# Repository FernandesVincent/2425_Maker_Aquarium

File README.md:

<header style="
      background-color: #004080;
      color: white;
      padding: 1rem;
      text-align: center;
      height: auto;">
<div class="header-title">
<h1>Aquarium Automatisé</h1>
</div>
</header>

SOMMAIRE
- Préambule
- Objectifs du projet
- Meuble
- Filtration
- Test en gouttes
- Raspberry Pi
- PCB
- Écrans
- Code
- Câblage
- Résultat et Conclusion
- Futur du projet
<h1 style="text-align: center; text-decoration: underline; font-weight: bold;">Préambule</h1>
Aujourd'hui, lorsqu'un particulier achète son aquarium il doit pouvoir gérer un nombre important de facteurs comme la température du bac, la distribution de la nourriture mais également les différents test que peux nécessité son Aquarium (ph, NO2, CO2, etc...). C'est donc dans l'idée de soulager les personnes que cela pèse de devoir s'occuper de tout ça que l'idée du projet d'aquarium automatisé et connecté m'est venue à l'esprit.
<h1 style="text-align: center; text-decoration: underline; font-weight: bold;">Objectifs du Projet</h1>
Pour répondre à la problématique énoncée durant le préambule, j'ai dessiné les différents axes et objectifs du projet énoncés ci-dessous:
- Automatisation des changements d'eau
- Contrôle simple et total sur la luminosité
- Automatisation de la distribution de la nourriture
- Automatisation des test en gouttes
- Contrôle simple de la température
- Afficher le tout sur des écrans
- Bonus : Créer une Application mobile
Afin de réaliser l'ensemble de ces objectifs, j'ai du mettre en oeuvre plusieurs compétences que j'ai pu apprendre durant mon cursus à l'ENSEA telles que:
- Découpe LASER
- Conception de PCBs
- Modélisation et impression 3D
- Sertissage de câbles
- Mécanique
- Soudure
Mais également de nouvelles comme le montage vidéo et le HTML/CSS/JS pour la création d'un site. Pour expliquer chaque partie de ce projet en détail, nous allons partir du plus gros oeuvre vers le plus petit. Commençons donc par parler du meuble qui doit supporter l'aquarium.
<h1 style="text-align: center; text-decoration: underline; font-weight: bold;">Meuble</h1>
Au vu de l'ensemble des objectifs du projet, il fallait un endroit où ranger notamment, l'électronique avec les PCBs et les câbles, le bloc de filtration externe, le dispositif d'analyse des test en gouttes ainsi que les bacs de changements d'eau. Pour répondre à ce besoin j'ai penser à la création d'un meuble pouvant supporter le poids de l'aquarium ainsi que tout ce qu'il y a à l'intérieur. Pour ce faire il a été décidé que la structure du meuble se ferait à l'aide de profilé aluminium 20x40mm et que les murs seront faits en MDF 3mm. Cependant quelques contraintes étaient présentes:
- le meuble doit au minimum faire la largeur (30cm) et la longueur(60cm) de l'aquarium.
- Il doit pouvoir accueillir 2 bacs ayant au minimum une capacité de 18L.
- Le bac doit être assez petit pour diminuer les coûts liés au profilé aluminium.
Prenant tout cela en compte, j'ai réalisés des premiers modèles 3D pour pouvoir estimer la taille du meuble et la quantité de profilé aluminium ainsi que de MDF nécessaire. Vous pouvez voir les modèles prototypes ci-dessous:
<table>
<tbody>
<tr>
<td></td>
<td></td>
<td></td>
</tr>
</tbody>
</table>
<table>
<tbody>
<tr>
<td></td>
<td></td>
<td></td>
</tr>
</tbody>
</table>
La version finale étant la suivante :

L'ensemble des fichiers STL est disponible sur mon
<a href="https://github.com/FernandesVincent/2425_Maker_Aquarium">GitHub</a>
dans la catégorie "onshape".
Ce meuble est donc sur 2 étages, le premier étant un étage réservé aux trois bacs de changements d'eau. Chacun ayant un objectif unique:
<br/>
<br/>
Celui ci-dessous est dédié à l'eau usée de l'aquarium qui peut être réutilisée pour par exemple arroser ses plantes.

Le second présent ci-dessous est fait pour accueillir l'eau propre qui va venir remplacer l'eau usée.

Le troisième et plus petit doit est quant à lui réservé à l'eau en sortie des test à gouttes qui doit être jetée.

Pour la sortie du premier bac j'ai trouver un modèle 3D de robinet qui fonctionne assez bien sur
<a href="https://www.printables.com/model/278618-water-tap">Printables</a>
.
De même que précédemment l'ensemble des fichiers STL mais également les fichiers DXF sont disponibles sur mon
<a href="https://github.com/FernandesVincent/2425_Maker_Aquarium">GitHub</a>
dans la catégorie "onshape".
<h1 style="text-align: center; text-decoration: underline; font-weight: bold;">Filtration</h1>
<br/>
Attaquons le second étage du meuble par la partie concernant le bloc de filtration. J'ai souhaité faire ce bloc externe moi-même car cela me permettait de créer un design personnalisé, notamment pour pouvoir y placer aisément le chauffage et la sonde ph en plus des masses filtrantes.
<br/>
Comme précédemment vous pouvez voir ci-dessous le prototype de ce bloc de filtration suivi de la version finale,
<br/>
<br/>
prototype:

<br/>
version finale:

<br/>
<br/>
Pour pouvoir nettoyer les masses filtrantes, j'ai designer un bac de remonté (trouer pour que l'eau s'en écoule et ne pas trempé le meuble en les sortant) avec sa poignée :
<table>
<tbody>
<tr>
<td></td>
<td></td>
</tr>
</tbody>
</table>
<br/>
<br/>
Concernant les différents composants de ce bloc, la sonde ph vient de
<a href="https://wiki.dfrobot.com/Gravity__Analog_Spear_Tip_pH_Sensor___Meter_Kit__For_Soil_And_Food_Applications__SKU__SEN0249">DFRobot</a>
tandis que le chauffage est fournis avec l'aquarium qui est un aquarium de 60L de la marque CIANO disponible sur
<a href="https://www.amazon.fr/Aquarium-Poissons-Consommables-Chauffage-Emballage/dp/B0DMZ6JCDD/?_encoding=UTF8&amp;pd_rd_w=eTX08&amp;content-id=amzn1.sym.46807d81-91bd-498b-9732-d523d8e7a752%3Aamzn1.symc.fc11ad14-99c1-406b-aa77-051d0ba1aade&amp;pf_rd_p=46807d81-91bd-498b-9732-d523d8e7a752&amp;pf_rd_r=917652W8GSPYV4HS716T&amp;pd_rd_wg=m7z8E&amp;pd_rd_r=916570f0-c766-4f99-b61e-7f823d6b24d8&amp;ref_=pd_hp_d_atf_ci_mcx_mr_ca_hp_atf_d&amp;th=1">Amazon</a>
.
<br/>
De plus, concernant les masses filtrantes elles sont également disponibles sur Amazon:
<a href="https://www.amazon.fr/Fluval-Pr%C3%A9filtre-pour-Aquariophilie-750/dp/B001CZXZEU?crid=2DO1R98ZQM2RC&amp;dib=eyJ2IjoiMSJ9.NOtwUJAeSHLB4A1TeyF7lMZri_mYYibux8elORv2TfHT8yLHpVdMSdJHqTUiYHcFMGr334v6IEnsWWmJfPLGE1mpoogN8XoEghupyyNrigO5VS3plDP2CcTmYq2QG4MJTkvTzTTOcQFQ4Y0zzN6mUG_yH7nay19Ffslt9v3t-JCdI6s2QMdTKHUrgb4h_1CvccY8n2z9cqhy9a3K2YmWuXX8cIhYSCcO7GUgdoUt6KjcFyZBTqqU88QPV-2foIqJT7tRuESUFezL2JtSR4yoJJafDqbmSgWf8wqJXLkooE1-nc9v4LDAB3mVxILasvuHKCNPN2AHisuPH9ZROWr5dpat5z9vd5tvAiF1vmKVE2g3hL_7fAWg2CkyKnFiSWWdrk5zkhM4B4p-2tI30VVCbNROYQcaY3yV6V1a9vud8sK52BZ7lmUmHwG4r6HhVILX.sY-sm_8FTIMCC4HghsrVIvfEG4izV4uUMwokH-4gn60&amp;dib_tag=se&amp;keywords=ceramique%2Bfiltre%2Baquarium&amp;qid=1740995166&amp;sprefix=ceramique%2Bfiltre%2Baquarium%2Caps%2C81&amp;sr=8-1&amp;th=1">céramique</a>
;
<a href="https://www.amazon.fr/cyclingcolors-d%C3%A9couper-300x210mm-Universelle-%C3%A9paisseur/dp/B0B8JQTZXK?__mk_fr_FR=%C3%85M%C3%85%C5%BD%C3%95%C3%91&amp;crid=1GWVJFUSDAMSF&amp;dib=eyJ2IjoiMSJ9.-Nc9EyO1uODmLOWsuEoIv2-ijdhS7vjX1hI6M1EGydp_XFS0wtrzbE2jVMFgrEHocHL6DNbcq4DOPNmEpaNBjZdWuUZP7ZPMicQLsIZ90SWD_deMd8pHQZAqzOpOAZ4D1IFHZ2X0fnkMDess7XfQdBE53jzyoQ5U7YxbRgxUxo4TxXIPRLPpCA1pShM8uPEC_14BnQmFSo0ENJEtF6zNZXzpbQdPOGYKqjRVUeZF0_ePPmf3qAuxzeko5WCX9S8S1h26QB7Ui_yH5xzVT67D3-7iV_G0tFTnQTAvHnabRmVddSMM1xzyo7R-AJKU_j0SQG36PPXQcBq1ewFXpCj_3ksSo4r8ET7GnpSYFM6XmYWrbgCw1QJ-D-15VbdYH-UsJ4eVRgI1szYcRs2AKRRBLG8D_Ecth-nHQBS7rLAzYn_QlE0Hg81ooezR5RGuDtZn.uqiGKSbLIfv1qsK1z4Wm6e5aRRmxiQVxfnGUyDTqWIk&amp;dib_tag=se&amp;keywords=mousse+filtration+aquarium&amp;qid=1740746478&amp;sprefix=mousse+filtration+aquarium%2Caps%2C86&amp;sr=8-10">mousse</a>
.
<br/>
Les trous dans le Blocs de filtration servent à le fixer dans le plancher à mi hauteur du meuble, ils correspondent à des vis de taille M6 avec une longueur qui doit être d'environ 20 mm sachant que le plancher est fait en MDF 6mm. Des écrous adéquat sont aussi à prévoir.
<br/>
Concernant l'impression du bloc de filtration, elle peut se faire en plus ou moins de parties en fonction de la taille de l'imprimantes. Par exemple, avec les imprimantes disponibles à l'ENSEA :
<br/>
<br/>
Creality K1 Max (300x300x300mm) : 2 parties
<br/>
BambuLab X1 Carbon(250x250x250mm) : 4 parties (les 2 parties précédentes doivent être coupées à mi-hauteur)
<br/>
<br/>
De plus, le bloc a été imprimé en PLA, or le PLA n'est pas étanche. Pour pallier à ce problème j'ai pris l'initiative d'utiliser de la résine époxy afin de vernir le bloc et de le rendre étanche. Le seul inconvénient de cette méthode est la toxicité de la résine notamment durant la phase de catalyse qui peut durer plusieurs heures et nécessite le port d'un
<a href="https://www.amazon.fr/AirGearPro-Protection-Respiratoire-R%C3%A9utilisable-poussi%C3%A8re/dp/B08BQNKK8D/ref=sr_1_12?crid=3LH54H1JA5QNK&amp;dib=eyJ2IjoiMSJ9.vwG9ct7oYhsXxHkosVw_DmGGbSvG-EdfTzmpbvbIy_-blRdYccvxTNdLoztSTV8tl_ikyBC3C5sx3ez7fd9GjM_BHjicTpMb-_M9EWASUwky-py3WhngzjeKjcqC1QPGVSqLLVt9dwrGpRvv8uZhM5_Re66P_tbjd75zfz0It3lw5R378O4styzF4mT2UFgELnVqo1dEaq5sjsjGSO8SU83Srj58_ZeWd_S_6tQwyARHEVkMqt6VuIe_q-BQpZhJykYvcj-rFgzkfMzgAcjRl5SiAw0cAYN1tXGGBibU2ro.akVBE5KxVIQV9yLbv8nGTHnn1ifGuOQN2ryeAmktGkY&amp;dib_tag=se&amp;keywords=masque%2Ba%2Bgaz&amp;qid=1745913052&amp;sprefix=masque%2Ba%2B%2Caps%2C88&amp;sr=8-12&amp;th=1">masque</a>
et de
<a href="https://www.amazon.fr/ARNOMED-jetables-pi%C3%A8ces-nitrile-disponibles/dp/B093SWH4D8/ref=sr_1_8_mod_primary_new?crid=2KVGNDRFCIO71&amp;dib=eyJ2IjoiMSJ9.HYDeG_JqkiNaNzhkKCJYphhk3ndVM0UbqT-yoTDSnaWFA6OdHlNBi3FhoeW2ZUUI0AozoLPBT0LRJtSUa-ADjaOinG8uifUUo70TLPnk6H4vzPfIN_jZfhI2XwAXMrE8QZiC77FgNaG4N8q-fSoo0epvPihgD-rdkskBYnW7LVj1pTZO8u1pXD_ZNOCaioAR9EvJmOK1yNxrAvVQc99SmUWtKPwbwy0ztc6t6WeLP1m2mzQK-hKjnMPUpVIE1dcgy_K40Tb25gJmvBveADWoAOuMog-kQ_XCkylXwUWTjHc.5SfCoj71a8R3wwyGeR2RD5FM8fDVUkjrGQuWOm_lA1U&amp;dib_tag=se&amp;keywords=gants%2Bnitrile&amp;qid=1745913117&amp;sbo=RZvfv%2F%2FHxDF%2BO5021pAnSA%3D%3D&amp;sprefix=gants%2Caps%2C93&amp;sr=8-8&amp;th=1">gants de protection</a>
.
<br/>
<br/>
Pour finir, l'eau arrive du côté de la sonde PH via un tuyaux avec un OD de 20mm et elle ressort de l'autre côté grâce à une pompe de remontée connecter via un raccord à un autre tuyaux.
<br/>
<br/>
<h1 style="text-align: center; text-decoration: underline; font-weight: bold;">Test en gouttes</h1>
Au sein du meuble et à côté du bloc de filtration nous pouvons retrouver la partie test en gouttes du projet. Cette partie est surement la plus complexe du projet car elle implique la modélisation 3D d'un dispositif permettant d'insérer et d'enlever les test en gouttes mais également de pouvoir faire tomber des gouttes lorsque l'on le désire.
<br/>
<br/>
La version actuelle a été réfléchie avec un servomoteur FS90 actionnant un engrenage qui permet à son tour de faire tourner des "bras" qui iront appuyer sur les test afin de faire tomber les gouttes.

<br/>
<br/>
Ce mécanisme est malheuresement encore en phase de prototypage car la faible tension de surface au niveau de la sortie goutte à goutte des test implique qu'une seule petite vibration peut faire s'écouler une goutte.
<br/>
Un autre modèle possible serait de faire directement tourner les tests via un servomoteur afin de faire s'écouler la goutte en profitant justement de la faible tension de surface.
<br/>
<br/>
Une fois la goutte écoulée, elle est redirigée dans un flacon, dans lequel s'écoule également l'eau du bac a testée, qui est bloqué par un anneau lié à un autre servomoteur lui permettant de pivoter afin de remuer la solution et enfin de vider le flacon dans un tuyaux menant au bac associé. Afin de déterminer la valeur associé au test (valeur de Ph, de NO3, etc...) il faut effectuer de la reconnaissance colorimétrique.
<h1 style="text-align: center; text-decoration: underline; font-weight: bold;">RaspberryPi</h1>
Pour effectuer la reconnaissance colorimétrique je me suis servi d'un raspberryPi 4 model B avec la module caméra associé. Cet ensemble auquel on ajoute un code en Python, disponible sur mon
<a href="https://github.com/FernandesVincent/2425_Maker_Aquarium">GitHub</a>
dans la catégorie "software", permet de récupérer la vision de la caméra et d'y définir un ou plusieurs points où l'on va vouloir analyser la couleur du pixel en leur centre :

<br/>
Le code couleur que j'ai utilisé est le HSV et non le RGB car cela permet d'être moins sensible à la différence de luminosité.

<br/>
<br/>
Un aspect que je n'ai pas eu le temps de terminer est le fait de comparer les valeurs récupérés par la caméra aux valeurs de références des couleurs des test en gouttes. Cependant, l'idée derrière ce code serait d'avoir pour chaque test un tableau contenant les couleurs références et ainsi via un petit d'algorithme de comparer la couleur HSV expérimental avec celle de référence afin de l'assimiler à celle-ci.
<br/>
Finalement il suffirait de faire correspondre la couleur HSV de référence avec la valeur associée. Une fois cela fait l'objectif est de transmettre cette valeur au PCB principal qui, lui, l'enverra aux écrans.
<h1 style="text-align: center; text-decoration: underline; font-weight: bold;">PCB</h1>
Cela nous fait une transition parfaite pour parler plus en profondeur de la partie PCB du projet. En effet, pour mener à bien ce projet j'ai du réaliser 2 PCB : un premier PCB dit "principal" et un second dit "déporté". Le premier PCB et son aspect de multiprise sert à commander l'ensemble du projet, c'est à dire :
<br/>
<br/>
- Les 4 ventilateurs
- Les 4 pompes
- Les LED
- Les servomoteurs pour le distributeur de nourriture/li>
- Les boutons présents sur le second PCB
- Les écrans
- Les servomoteurs pour les test en gouttes
- la raspberryPi et sa camera
- Les capteurs de niveau d'eau
- Le Ph-mètre
- Le chauffage
- Le ST-Link
- Le HC05
Faisons un petit aparté pour détailler l'utilité de chacun des modules dont nous n'avons pas encore eu l'occasion de discuter.
<br/>
<br/>
<h4>Ventilateurs</h4>
Le meuble et le PCB sont fait pour accueillir 4
<a href="https://www.amazon.fr/ARCTIC-P12-Pack-Refroidisseur-Ventilateur/dp/B07HC7P3HJ/ref=sr_1_22?__mk_fr_FR=%C3%85M%C3%85%C5%BD%C3%95%C3%91&amp;crid=3TXQLZO0PSBMV&amp;dib=eyJ2IjoiMSJ9.zUhrIjc32H8-WvshILuE-PtJkv-mw1FkSGAgT1AOR1oDyib-dphFTw_ivU8-Os2Z3SPkMx71hmaU-qOowlMbCeCCD-m-aEquUmbZ3FlHR8_-ej5oHyh2yaVaZolCfb03zDvlUppXXPbv_NlB8bF4hvQ0kXKkbZYUaWO43Sw08Tl8NM4P3ilE9XKvfy9u-lT4zo6KmAZJ5tKS3DDawNQxlgLpxpx_1iES2Xqx_mKGXe48RHJHkL_6mCOrnpOmsJY1jxpEXj42bwhzMWrXvfzqdaw7qTj1C8cfzn7Wl4qSAVI.Drgr1JScUsXTqbsAaerU-8GdExFSoYqVR8i45yJohCs&amp;dib_tag=se&amp;keywords=ventilateur+pc+120mm+12V&amp;qid=1745915029&amp;sprefix=ventilateur+pc+120mm+12v%2Caps%2C109&amp;sr=8-22">ventilateurs</a>
12V de 120mmx120mm. Deux (paire entrée/sortie) à l'étage des bacs et deux ( paire entrée/sortie) à l'étage supérieur.
<br/>
Le couple de ventilateur de l'étage inférieur a pour but de ventilé l'eau propre arrivant dans le bac associé afin d'aider à l'évaporation des éléments indésirables contenu dans cette eau (si on utilise de l'eau osmosée ces deux ventilateurs sont inutiles).
<br/>
Le second couple de moteur, quant à lui, est là pour aérer la Pi, le PCB et surtout l'alimentation qui ne possède pas de ventilateur.
<h4>
<br/>
</h4>
<h4>Pompes</h4>
Pour ce projet, nous avons besoins d'un ensemble de 4
<a href="https://www.amazon.fr/submersibles-aquarium-poissons-fontaine-divertissement/dp/B0CDK7GQF2/ref=sr_1_21?__mk_fr_FR=%C3%85M%C3%85%C5%BD%C3%95%C3%91&amp;crid=2CUWEXFG2PUFC&amp;dib=eyJ2IjoiMSJ9.kt5smPhlWur0wnbrli3H4DrVLEC06_QO_JbOBYEyMijIh7_RthNJVyfAX4Ud4PPDpqdHwQ4pOWaoo6zsfZ69VyOE8kOFChswIdw_yxYq4pP-k7e8YAFBlQMr3mmeVJtgOaJd2ZKn4M9ht6t596XUTjhOngGLBwXbttb6pcsssp_XBXbosgC-o98d1DYvuCTUCOvFmy3iTxm9IGIwgRYmeEGXowZ4qxU2LAg6pIt1ekSnjvASpDlITmRQtVY1Zr23BJv-VApa7OJQNyjO6xRdQ4rEIOZGFSaqHZtZlUoIaBo.5UAUpJxV19I-vKTE8ASD2hpe8OtvqdkrKyf74I9DL3Q&amp;dib_tag=se&amp;keywords=pompe+12v+eau&amp;qid=1745915095&amp;sprefix=pompe+12v+eau%2Caps%2C86&amp;sr=8-21">pompes</a>
12V 240L/h. Une première sert pour la sortie de la filtration, une seconde à remontée l'eau du bac d'eau propre à l'aquarium, une troisième à vider l'eau de l'aquarium vers le bac de récupération de l'eau usée et la dernière envoi l'eau vers le filtre. Les deux pompes liées à la filtrations fonctionnent en continu tandis que les deux autres fonctionne sur commande grâce à l'utilisation de deux transistors NMOS présents sur le PCB permettant d'allumer les pompes quand le GPIO lié à leur Ground est à l'état haut.
<h4>
<br/>
</h4>
<h4>LED</h4>
Les LED de ce projet sont séparées en deux parties mais viennent toutes de la même bande
<a href="https://www.amazon.fr/Jun-Saxifragelec-lumineuse-flexible-adressable-individuellement/dp/B0B8N4V9HW/ref=sr_1_7?__mk_fr_FR=%C3%85M%C3%85%C5%BD%C3%95%C3%91&amp;crid=1CJ3DP9KGQZX7&amp;dib=eyJ2IjoiMSJ9.jsv5HLdSZ_CqM09rG6Xk6uZZAWjjtuBx5FYoyybZ6Cq0dW9sdN0xiOcqO8t8Ln6LuHMjn9s3v2aI3iDoKG0TfEWM3Paz30Z6tmC2xSMbVQSZ50eRcyr4CrFsPwJ1RPR3CfkJwi70Efu_rKi0G0wMe0WJ2qUvEkmbGIRzA1bnyN1mzGsZ2Wg8r_ZL_B7AHo-iN01WSayc71oC5XkE90xITgpsP5gH7CkykDFgiCTTThXMaQrIhLf8PSJImtNxPoGk4S0CWjx7Hrr5ck_nuMyflQfhR7mZIpUyXcVC_EAC5UM.w_CUH-9CxgqyNuN4tKuXXqzRhF1nZa9Ggmml6dgE2r4&amp;dib_tag=se&amp;keywords=ruban%2Bled%2Bneopixel&amp;qid=1745915170&amp;sprefix=ruban%2Bled%2Bneopixel%2Caps%2C85&amp;sr=8-7&amp;th=1">Neopixel</a>
.
<h4>
<br/>
</h4>
<h5>LED internes</h5>
Ce sont des LEDs coupées du ruban et placées dans le meuble afin de pouvoir l'éclairer en continu avec une même luminosité afin de limiter au mieux les erreurs de reconnaissances colorimétriques.
<h4>
<br/>
</h4>
<h5>LED externes</h5>
Ces LED sont le reste du ruban et servent directement à l'éclairage de l'aquarium. L'utilité d'avoir pris des LED Neopxiel est ici de pouvoir totalement configurer la couleur que l'on veut pour éclairer son aquarium en fonction des poissons et plantes qui l'occupe.
<h4>
<br/>
</h4>
<h4>Servomoteurs (nourriture)</h4>
Je vais traiter directement ici la partie de la distribution automatique de la nourriture car je n'ai pas eu le temps de la réaliser et par conséquent elle ne nécessite pas une partie entière à elle seule. L'objectif de cette partie était initialement de pouvoir automatiser la distribution de nourriture via un système de courroie de transmission qui amène la nourriture depuis une entrée (image ci-dessous) jusqu'à une trappe qui s'ouvre ou se ferme via l'utilisation d'un servomoteur, le tout installé à l'intérieur de la ramp LED qui éclaire l'aquarium.
<br/>
<br/>
<br/>
Ce dispositif, au même titre que les bacs de changement d'eau, permettrait à l'usager de pouvoir partir en vacances ou autre tout en sachant que les poissons seront nourris et que les changements d'eau se feront. Le problème majeur qui a fait que je n'ai pas pu réaliser cette partie est la création de la courroie de transmission qui doit être assez petite pour pouvoir faire en sorte que la rampe LED ne devienne pas trop massive autant d'un point de vu visuel que du point de vu de sa masse.
<h4>
<br/>
</h4>
<h4>Boutons</h4>
Les boutons sont placés sur le PCB secondaire et sont au nombre de 6, 3 paires de 2 boutons. Chaque paire permet d'ajuster un paramètre, la première paire permet d'ajuster la température, la deuxième la température et la troisième la fréquence de la distribution de nourriture.
<h4>
<br/>
</h4>
<h4>Écrans</h4>
Le PCB secondaire est également connecté à 6
<a href="https://www.gotronic.fr/art-afficheur-oled-0-96-128-x-64-grove-33932.htm">écrans</a>
OLED dont l'objectif est d'afficher les différents paramètres de notre système, que ce soit la température, la luminosité ou bien els différents test de l'eau.
<h4>
<br/>
</h4>
<h4>Capteurs de niveau d'eau</h4>
Ces
<a href="https://www.adafruit.com/product/4965">capteurs</a>
servent, comme leur nom l'indique, à vérifier le niveau de l'eau. Je me suis procuré ceux de Adafruit car leur prix est peu élevé et qu'ils suffisent pour l'utilité que j'en ai.
<br/>
<br/>
Lorsque deux bandes de métal entrent en contact avec de l'eau cela crée un court-circuit ce qui renvoie un signal au PCB (état haut : il ya la présence de court circuit donc l'eau à atteint le niveau que l'on veut vérifier tandis qu'à l'état bas ce n'est pas le cas). J'ai prévu d'en placer un dans l'aquarium, un autre dans le bac d'eau usée et un dernier dans le bac d'eau propre. Tout les trois servant à indiquer que l'on a atteint une hauteur limite au dessus de laquelle il se peut que l'eau se déserve des bacs.
<h4>
<br/>
</h4>
<h4>Ph-mètre</h4>
Ce Ph-mètre est fournis avec la sonde Ph et permet de rendre lisible la tension que sort la sonde Ph. Dans le futur du projet il me plairait de réussir à en faire un moi même.
<h4>
<br/>
</h4>
<h4>Chauffage</h4>
Fournis avec l'aquarium, l'objectif serait d'y connecter un servomoteur afin de pouvoir sélectionner la température que l'on souhaite avec le module externe où se trouve le PCB déporté ainsi que les écrans.
<h4>
<br/>
</h4>
<h4>ST-Link</h4>
Simplement présent pour pouvoir programmer le microprocesseur.
<h4>
<br/>
</h4>
<h4>HC05</h4>
J'ai prévu un connecteur pour le module HC05 même si l'utilisation de celui-ci ne se fera qu'à la toute fin du projet. L'objectif étant de connecter un pc ou un téléphone en bluetooth à ce module afin de récupérer l'ensemble des paramètres comme le font les écrans mais cette fois sur un pc ou un téléphone, l'objectif ultime étant le développement d'une appilcation.
<br/>
<br/>
<br/>
<br/>
<br/>
Revenons en aux PCBs, vous l'aurez compris mais ici nous avons 2 PCB avec des rôles bien distinct, le premier servant à contrôler l'ensemble du projet tandis que le second ne gère que les boutons et à se connecter aux écrans. Vous pouvez trouver ci-dessous deux photos par PCB suivies d'un lien, les photos correspondent aux schemtatic et routage des PCB effectués sous KiCad 9.0 et le fichier quant à lui est la Bill Of Material (BOM) contenant l'ensemble des composants nécessaires à la fabrication des PCB.
<br/>
<br/>
PCB principal:
<table>
<tbody>
<tr>
<td></td>
<td></td>
</tr>
</tbody>
</table>
<a href="https://github.com/FernandesVincent/2425_Maker_Aquarium/blob/main/hardware/PCB_Aquarium2/BOM_PDF.pdf">BOM</a>
<br/>
<br/>
PCB secondaire:
<table>
<tbody>
<tr>
<td></td>
<td></td>
</tr>
</tbody>
</table>
<a href="https://github.com/FernandesVincent/2425_Maker_Aquarium/blob/main/hardware/PCB_secondaire/BOM_PDF.pdf">BOM</a>
<h1 style="text-align: center; text-decoration: underline; font-weight: bold;">Écrans</h1>
Nous avons d'ores et déjà parlé succinctement du rôle des écrans dans le projet c'est pourquoi j'aimerais m'attarder ici plutôt sur la partie code associé à ces écrans. En effet, Les écrans que j'ai commandé sont les suivants:
<br/>
<br/>
Ces écrans peuvent communiquer soit en I2C (avec 2 adresses possibles : 0x7A et 0x78) soit en SPI. Or, et je pense que vous l'avez compris avec la partie précédente mais nous avons beaucoup de modules différents avec lesquels le microprocesseur doit communiquer. Le microprocesseur en question est le STM32G474RET6 qui possède 3 I2C, ce qui est parfait pour notre projet car nous pouvons commander 2 écrans avec un seul I2C. Mais à cause du nombre très élevés du nombre de pins que le microprocesseur doit allouer au reste du projet, les pins que les 3 I2C utilisent ne sont plus disponibles.
<br/>
Il m'a donc fallu me rabattre sur le SPI qui bien que nécessitant un nombre de pins plus élevés est plus pratique dans ce cas pour deux : 1 seul SPI peut gérer les 6 écrans à conditionner de leur réservé un pin de sélection (Chip Select (CS)) chacun mais également car la plupart des pins qu'il utilise peuvent être de simple GPIO (comme CS) voir même non obligatoire en fonction de l'utilisation.
<br/>
Par exemple dans notre cas nous n'avons pas besoin du pin MOSI (Master Out Slave In) car on attend pas de réponse de la part des écrans.
<br/>
Le problème majeur que j'avais concernant le SPI est que je n'avais jamais travaillé ce protocole auparavant, j'ai donc du apprendre comment il fonctionne ce qui ne fut, heureusement, pas la partie la plus compliquée. Cependant, là où je me suis heurté à un mur c'est au moment de la recherche de librairies pour utiliser ce protocole avec le driver de mes écrans (le SSD1315) qui n'est malheureusement pas le driver le plus utilisé ce qui implique donc que les librairies que j'ai trouvées n'avaient pas directement de librairies pour ce driver, même si il semblerait que celles du driver SSD1306 fonctionne, du moins en partie, avec le SSD1315. De plus, j'ai également reçu de la part de mon encadrant une library faîte pour mon driver mais en I2C.
<br/>
Au vu du temps qu'il me restait à ce moment là j'ai préféré me concentrer sur d'autres aspects du projet ce qui fait qu'à l'heure où j'écris ces lignes, les écrans ne sont pas encore fonctionnels.
<h1 style="text-align: center; text-decoration: underline; font-weight: bold;">Code</h1>
Nous avons déjà eu l'occasion d'aborder le sujet du code dans ce projet mais j'aimerais y dédier une partie car il y a quand même des notions à ajouter et que je ne pourrais diluées dans aucune aitre partie. Veuillez tout d'abord regarder le diagramme d'architecture du code présent ci-dessous:

<br/>
Nous avons déjà aborder la partie de la RaspberryPi excepté le fait que pour effectué la reconnaissance colorimétrique j'ai du utiliser OpenCV.
<br/>
<br/>
Concernant le code du STM32 il est, je pense, nécessaire de recontextualiser: Pour ce projet nous devons effectué des changements d'eau à un intervalle fixe (10% de l'eau de l'aquarium chaque semaine), de même il faut nourrir les poissons et effectuer les test en gouttes à intervalles réguliers. Pour effectuer cela sachant que le projet n'est pas connecté à Internet, il m'a fallu créer un horloge interne qui peux fonctionner d'elle même après avoir flasher le microprocesseur avec le code présent sur mon PC. Le fichier la contenant peut être trouver sur mon GitHub. Cette Horloge démarre à partir d'un date définit arbitrairement et permet de réaliser des actions du type : si on est au jour X à l'heure Y et à la minute Z : fait telle action.
<br/>
De plus, comme je ne commande en moteur que des servomoteurs basiques, il me suffit de leur envoyer des PWMs pour définir la position d'arrivé et ensuite les faire revenir à leur positions de départ une fois leur action finie. Le seul inconvénient de cela est que dois tester chaque mouvement de mes servomoteurs pour plusieurs valeurs de PWMs afin de pouvoir savoir quelle valeur de PWM serait la meilleure. Une méthode plus évoluée serait de créer une boucle for qui incrémente la valeur de la PWM à chaque itération.
<br/>
Finalement, Les LEDs sont commandées via DMA grâce à une librairie crée par l'un des professeurs de l'école. La seule chose est que je dois définir des valeurs références pour la couleur des LEDs afin que l'usager puisse par l'appui des boutons, passer d'une couleur à une autre. Une amélioration serait d'avoir 3 encodeur rotatif permettant à l'usager d'avoir la possibilité de régler la couleur de la lumière de son précision avec une précision qu'il n'a pas actuellement.
<h1 style="text-align: center; text-decoration: underline; font-weight: bold;">Câblage</h1>
Au vu du projet et du nombre de modules à connecter aux PCB vous vous doutez que le nombre de câbles à sertir est conséquent ! Et c'est effectivement le cas.
<br/>
Pour ce projet j'ai du sertir énormément de câbles pour différents types de connecteurs : JST EH, JST XH, Duponts. De plus, j'ai également du simplement dénuder des câbles afin de pouvoir les souder à d'autres notamment pour les pompes ou les câbles d'alimentation.
<br/>
Mais le câblage ne s'arrête pas à sertir un câble, il faut également les emballer. C'est à dire qu'il faut entourer les câble de gaine tressée pour les protéger mécaniquement et thermiquement mais également pour les organiser. Mais il faut également les entourer de gaine thermorétractable pour fixer la gaine tressée aux câbles au niveau des extrémités pour pas qu'elle ne bouge mais également au niveau des points de soudure pour protéger ce point notamment si il y a un autre câble souder à côté, ils sont ainsi isolés l'un de l'autre et l'on ne risque pas de mauvais contacts.
<h1 style="text-align: center; text-decoration: underline; font-weight: bold;">Résultat Final et Conclusion</h1>
Tout au long de cette présentation vous avez pu voir différentes parties du projet mais il est temps de montrer le résultat que j'ai réussi à obtenir à la fin de ce proje ainsi que la vidéo de présentation du projett:
<br/>
<a href="https://github.com/FernandesVincent/2425_Maker_Aquarium/blob/main/gestion%20projet/final%20result.mp4">
<br/>Résultat final</a>
<br/>
<a href="https://github.com/FernandesVincent/2425_Maker_Aquarium/blob/main/gestion%20projet/Vid%C3%A9o%20Aquarium.mp4">vidéo de présentation</a>
<br/>
<br/>
Comme vous pouvez le voir je n'ai pas pris de vidéos avec l'aquarium remplit et le système en fonctionnement et la raison à cela est simple: je n'ai pas réussi à finir et emboiter toutes les parties du projet dans le temps impartit.
<br/>
<br/>
Pour conclure cette présentation j'aimerais revenir sur ce qu'à pu m'apporter ce projet. En effet, ce projet malgré le fait que je n'ai pas pu le finir m'a quand même permis de développer toutes les compétences que l'on a pu développées au cours de cette présentation, des compétences que j'avais déjà mais que j'ai pu grandement améliorées comme la création et la soudure de PCB ou bien des compétences que je n'avais pas encore eu l'occasion de développer durant mon parcours comme la découpe LASER, la modélisation et l'impression 3D.
<br/>
Au vu de mon niveau, ce projet était sans nul doute ambitieux, surement trop d'ailleurs au vu du temps impartit mais c'est ce qui en fait un bon projet dans le sens où j'ai pu apprendre comme je n'ai jamais appris avec n'importe quel autre projet.
<h1 style="text-align: center; text-decoration: underline; font-weight: bold;">Futur du Projet</h1>
Bien évidemment je ne compte pas m'arrêter là pour ce projet. En effet, il me reste un an pour le finir avant de finir mes études et je compte bien profiter de cette année pour finir le projet et y apporter toutes les améliorations dont j'ai pu parler au sein de cette présentation et qui sait peut-être que d'autres me viendront à l'esprit entre temps !

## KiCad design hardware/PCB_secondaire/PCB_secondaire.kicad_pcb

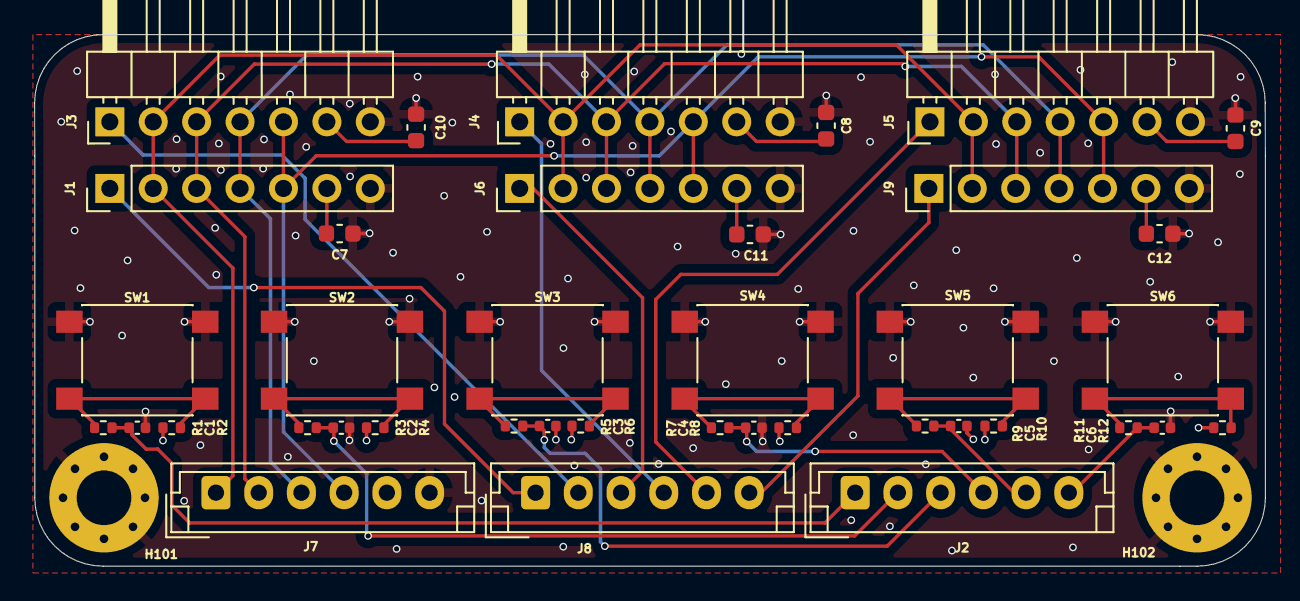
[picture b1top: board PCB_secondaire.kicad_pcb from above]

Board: 4 copper layers, 72.0 x 31.1 mm, 41 parts (0 on the bottom side), 24 nets.

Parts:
C1, C2, C3, C4, C5, C6: 10n; C_0402_1005Metric
C7, C8, C9, C10, C11, C12: 1u; C_0603_1608Metric
H101, H102: MountingHole_Pad; MountingHole_3.2mm_M3_Pad_Via
J1, J6, J9: Conn_01x07; PinHeader_1x07_P2.54mm_Vertical
J2, J7, J8: Conn_01x06; JST_EH_B6B-EH-A_1x06_P2.50mm_Vertical
J3, J4, J5: Conn_01x07; PinHeader_1x07_P2.54mm_Horizontal
R1, R2, R3, R4, R5, R6, R7, R8, R9, R10, R11, R12: 10k; R_0402_1005Metric
SW1, SW2, SW3, SW4, SW5, SW6: SW_SPST; SW_Push_1P1T_NO_6x6mm_H9.5mm

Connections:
+3.3V: C7.2, C8.2, C9.2, C10.2, C11.2, C12.2, J1.6, J3.6, J4.6, J5.6, J6.6, J7.5, J9.6, R2.1, R4.1, R6.1, R8.1, R10.1, R12.1
/SPI_CS_1: J1.1, J8.1
/SPI_CS_2: J3.1, J8.2
/SPI_CS_3: J6.1, J8.3
/SPI_CS_4: J4.1, J8.4
/SPI_CS_5: J5.1, J8.5
/SPI_CS_6: J8.6, J9.1
/SPI_D/C: J1.2, J3.2, J4.2, J5.2, J6.2, J7.1, J9.2
/SPI_MOSI: J1.4, J3.4, J4.4, J5.4, J6.4, J7.3, J9.4
/SPI_RES: J1.3, J3.3, J4.3, J5.3, J6.3, J7.2, J9.3
/SPI_SCK: J1.5, J3.5, J4.5, J5.5, J6.5, J7.4, J9.5
BTN_1: C1.1, J2.1, R1.2
BTN_2: C2.1, J2.2, R3.2
BTN_3: C3.1, J2.3, R5.2
BTN_4: C4.1, J2.4, R7.2
BTN_5: C5.1, J2.5, R9.2
BTN_6: C6.1, J2.6, R11.2
GND: C1.2, C2.2, C3.2, C4.2, C5.2, C6.2, C7.1, C8.1, C9.1, C10.1, C11.1, C12.1, H101.1, H102.1, J1.7, J3.7, J4.7, J5.7, J6.7, J7.6, J9.7, SW1.2 (B), SW2.2 (B), SW3.2 (B), SW4.2 (B), SW5.2 (B), SW6.2 (B)
unnamed: R1.1, R2.2, SW1.1 (A)
unnamed: R3.1, R4.2, SW2.1 (A)
unnamed: R5.1, R6.2, SW3.1 (A)
unnamed: R7.1, R8.2, SW4.1 (A)
unnamed: R9.1, R10.2, SW5.1 (A)
unnamed: R11.1, R12.2, SW6.1 (A)

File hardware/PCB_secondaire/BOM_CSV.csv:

"Reference","Qty","Value","Footprint"
"C1,C2,C3,C4,C5,C6","6","10n","Capacitor_SMD:C_0402_1005Metric"
"C7,C8,C9,C10,C11,C12","6","1u","Capacitor_SMD:C_0603_1608Metric"
"H101,H102","2","MountingHole_Pad","MountingHole:MountingHole_3.2mm_M3_Pad_Via"
"J1,J6,J9","3","Conn_01x07","Connector_PinHeader_2.54mm:PinHeader_1x07_P2.54mm_Vertical"
"J2,J7,J8","3","Conn_01x06","Connector_JST:JST_EH_B6B-EH-A_1x06_P2.50mm_Vertical"
"J3,J4,J5","3","Conn_01x07","Connector_PinHeader_2.54mm:PinHeader_1x07_P2.54mm_Horizontal"
"R1,R2,R3,R4,R5,R6,R7,R8,R9,R10,R11,R12","12","10k","Resistor_SMD:R_0402_1005Metric"
"SW1,SW2,SW3,SW4,SW5,SW6","6","SW_SPST","mylib:SW_Push_1P1T_NO_6x6mm_H9.5mm"

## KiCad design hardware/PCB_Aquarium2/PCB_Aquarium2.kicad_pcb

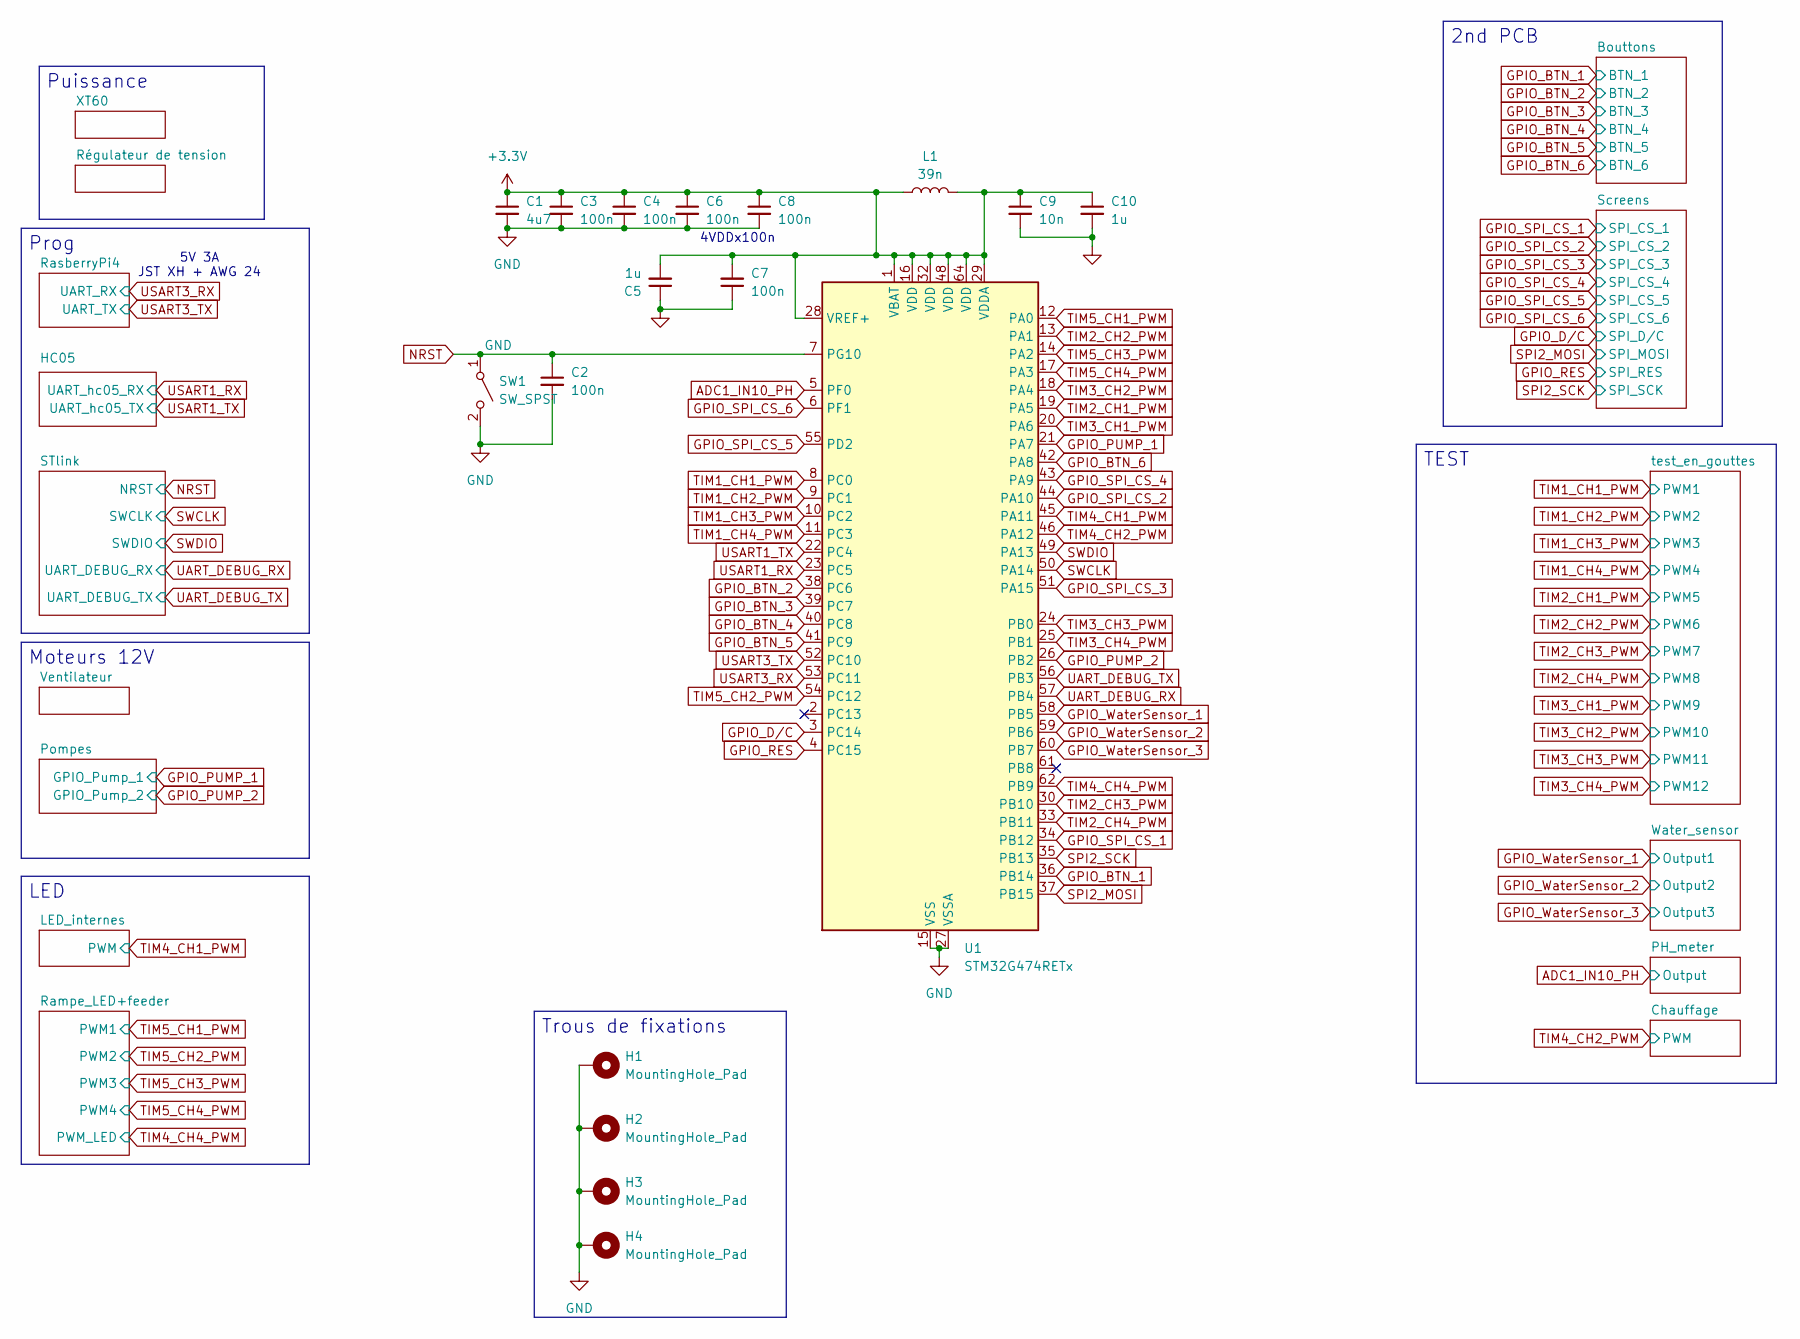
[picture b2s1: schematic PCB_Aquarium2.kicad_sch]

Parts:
C1: 4u7; C_0603_1608Metric
C2, C3, C4, C6, C7, C8: 100n; C_0402_1005Metric
C5, C10: 1u; C_0603_1608Metric
C9: 10n; C_0402_1005Metric
H1, H2, H3, H4: MountingHole_Pad; MountingHole_3.2mm_M3_Pad_Via
L1: 39n; L_0805_2012Metric
SW1: SW_SPST; SW_Push_1P1T_NO_6x6mm_H9.5mm
U1: STM32G474RETx; LQFP-64_10x10mm_P0.5mm

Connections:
+3.3V: C1.1, C3.1, C4.1, C5.2, C6.1, C7.2, C8.1, C9.1, C10.1, L1.1, L1.2, U1.1 (VBAT), U1.16 (VDD), U1.28 (VREF+), U1.29 (VDDA), U1.32 (VDD), U1.48 (VDD), U1.64 (VDD); also elsewhere on the board
ADC1_IN10_PH: U1.5 (PF0); also elsewhere on the board
GND: C1.2, C2.2, C3.2, C4.2, C5.1, C6.2, C7.1, C8.2, C9.2, C10.2, H1.1, H2.1, H3.1, H4.1, SW1.2 (B), U1.15 (VSS), U1.27 (VSSA), U1.31 (VSS), U1.47 (VSS), U1.63 (VSS); also elsewhere on the board
GPIO_BTN_1: U1.36 (PB14); also elsewhere on the board
GPIO_BTN_2: U1.38 (PC6); also elsewhere on the board
GPIO_BTN_3: U1.39 (PC7); also elsewhere on the board
GPIO_BTN_4: U1.40 (PC8); also elsewhere on the board
GPIO_BTN_5: U1.41 (PC9); also elsewhere on the board
GPIO_BTN_6: U1.42 (PA8); also elsewhere on the board
GPIO_D/C: U1.3 (PC14); also elsewhere on the board
GPIO_PUMP_1: U1.21 (PA7); also elsewhere on the board
GPIO_PUMP_2: U1.26 (PB2); also elsewhere on the board
GPIO_RES: U1.4 (PC15); also elsewhere on the board
GPIO_SPI_CS_1: U1.34 (PB12); also elsewhere on the board
GPIO_SPI_CS_2: U1.44 (PA10); also elsewhere on the board
GPIO_SPI_CS_3: U1.51 (PA15); also elsewhere on the board
GPIO_SPI_CS_4: U1.43 (PA9); also elsewhere on the board
GPIO_SPI_CS_5: U1.55 (PD2); also elsewhere on the board
GPIO_SPI_CS_6: U1.6 (PF1); also elsewhere on the board
GPIO_WaterSensor_1: U1.58 (PB5); also elsewhere on the board
GPIO_WaterSensor_2: U1.59 (PB6); also elsewhere on the board
GPIO_WaterSensor_3: U1.60 (PB7); also elsewhere on the board
NRST: C2.1, SW1.1 (A), U1.7 (PG10); also elsewhere on the board
SPI2_MOSI: U1.37 (PB15); also elsewhere on the board
SPI2_SCK: U1.35 (PB13); also elsewhere on the board
SWCLK: U1.50 (PA14); also elsewhere on the board
SWDIO: U1.49 (PA13); also elsewhere on the board
TIM1_CH1_PWM: U1.8 (PC0); also elsewhere on the board
TIM1_CH2_PWM: U1.9 (PC1); also elsewhere on the board
TIM1_CH3_PWM: U1.10 (PC2); also elsewhere on the board
TIM1_CH4_PWM: U1.11 (PC3); also elsewhere on the board
TIM2_CH1_PWM: U1.19 (PA5); also elsewhere on the board
TIM2_CH2_PWM: U1.13 (PA1); also elsewhere on the board
TIM2_CH3_PWM: U1.30 (PB10); also elsewhere on the board
TIM2_CH4_PWM: U1.33 (PB11); also elsewhere on the board
TIM3_CH1_PWM: U1.20 (PA6); also elsewhere on the board
TIM3_CH2_PWM: U1.18 (PA4); also elsewhere on the board
TIM3_CH3_PWM: U1.24 (PB0); also elsewhere on the board
TIM3_CH4_PWM: U1.25 (PB1); also elsewhere on the board
TIM4_CH1_PWM: U1.45 (PA11); also elsewhere on the board
TIM4_CH2_PWM: U1.46 (PA12); also elsewhere on the board
TIM4_CH4_PWM: U1.62 (PB9); also elsewhere on the board
TIM5_CH1_PWM: U1.12 (PA0); also elsewhere on the board
TIM5_CH2_PWM: U1.54 (PC12); also elsewhere on the board
TIM5_CH3_PWM: U1.14 (PA2); also elsewhere on the board
TIM5_CH4_PWM: U1.17 (PA3); also elsewhere on the board
UART_DEBUG_RX: U1.57 (PB4); also elsewhere on the board
UART_DEBUG_TX: U1.56 (PB3); also elsewhere on the board
USART1_RX: U1.23 (PC5); also elsewhere on the board
USART1_TX: U1.22 (PC4); also elsewhere on the board
USART3_RX: U1.53 (PC11); also elsewhere on the board
USART3_TX: U1.52 (PC10); also elsewhere on the board

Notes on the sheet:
5V 3A JST XH + AWG 24
4VDDx100n
TEST
Puissance
LED
2nd PCB
Moteurs 12V
Trous de fixations
Prog

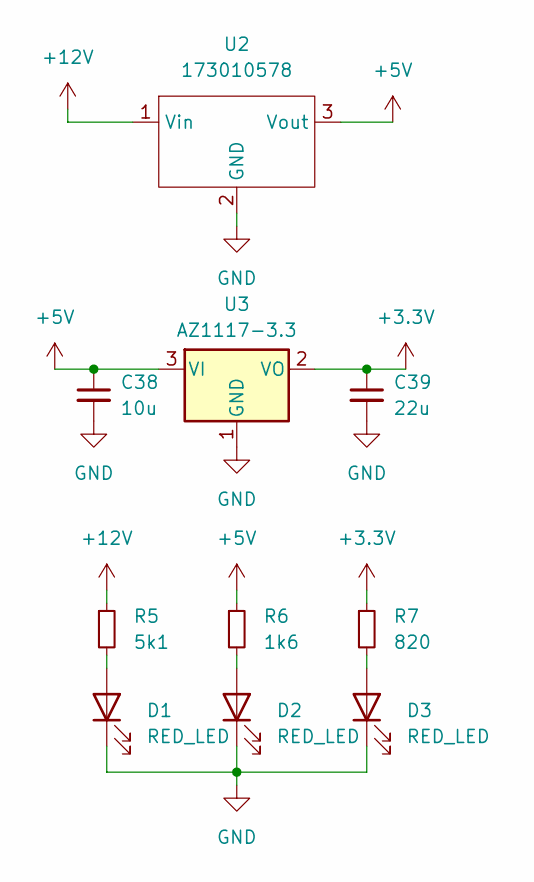
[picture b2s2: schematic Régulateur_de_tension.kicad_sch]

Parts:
C38: 10u; C_0603_1608Metric
C39: 22u; C_Elec_5x5.4
D1, D2, D3: RED_LED; LED_0603_1608Metric; MPN 150060RS55040
R5: 5k1; R_0402_1005Metric
R6: 1k6; R_0402_1005Metric
R7: 820; R_0402_1005Metric
U2: 173010578; 173010542; MPN 173010578
U3: AZ1117-3.3; SOT-223-3_TabPin2; MPN AZ1117CH2-3.3TRG1

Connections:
+3.3V: C39.1, R7.1, U3.2 (VO); also elsewhere on the board
+5V: C38.1, R6.1, U2.3 (Vout), U3.3 (VI); also elsewhere on the board
+12V: R5.1, U2.1 (Vin); also elsewhere on the board
GND: C38.2, C39.2, D1.1 (K), D2.1 (K), D3.1 (K), U2.2 (GND), U3.1 (GND); also elsewhere on the board
unnamed: D1.2 (A), R5.2
unnamed: D2.2 (A), R6.2
unnamed: D3.2 (A), R7.2

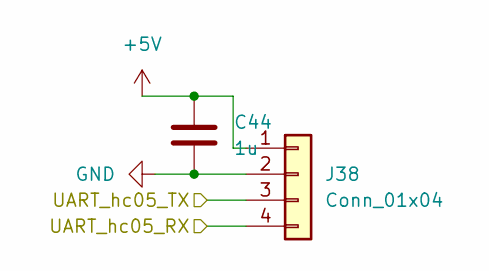
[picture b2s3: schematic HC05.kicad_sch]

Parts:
C44: 1u; C_0603_1608Metric
J38: Conn_01x04; JST_EH_B4B-EH-A_1x04_P2.50mm_Vertical

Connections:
+5V: C44.2, J38.1; also elsewhere on the board
GND: C44.1, J38.2; also elsewhere on the board
USART1_RX: J38.4; also elsewhere on the board
USART1_TX: J38.3; also elsewhere on the board

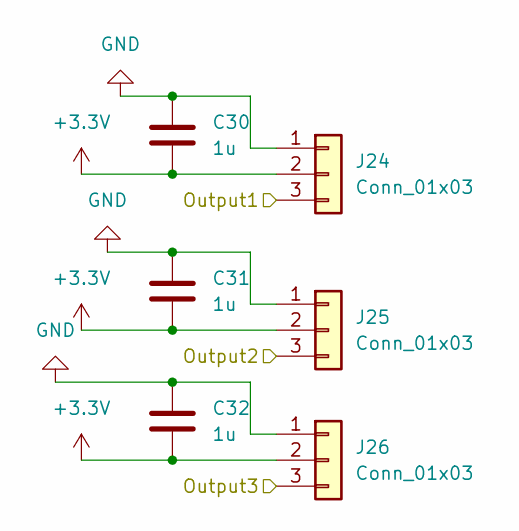
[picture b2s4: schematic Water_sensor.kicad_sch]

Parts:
C30, C31, C32: 1u; C_0603_1608Metric
J24, J25, J26: Conn_01x03; JST_EH_B3B-EH-A_1x03_P2.50mm_Vertical

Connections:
+3.3V: C30.1, C31.1, C32.1, J24.2, J25.2, J26.2; also elsewhere on the board
GND: C30.2, C31.2, C32.2, J24.1, J25.1, J26.1; also elsewhere on the board
GPIO_WaterSensor_1: J24.3; also elsewhere on the board
GPIO_WaterSensor_2: J25.3; also elsewhere on the board
GPIO_WaterSensor_3: J26.3; also elsewhere on the board

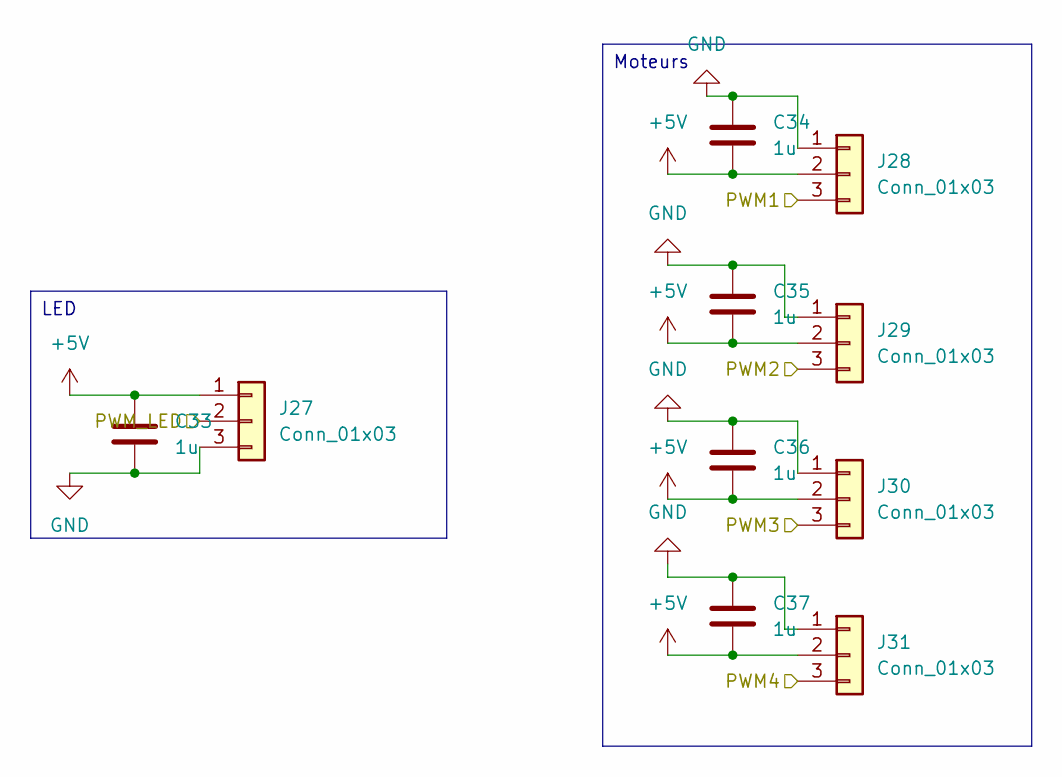
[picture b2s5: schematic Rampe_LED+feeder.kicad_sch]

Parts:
C33, C34, C35, C36, C37: 1u; C_0603_1608Metric
J27, J28, J29, J30, J31: Conn_01x03; JST_EH_B3B-EH-A_1x03_P2.50mm_Vertical

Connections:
+5V: C33.2, C34.1, C35.1, C36.1, C37.1, J27.1, J28.2, J29.2, J30.2, J31.2; also elsewhere on the board
GND: C33.1, C34.2, C35.2, C36.2, C37.2, J27.3, J28.1, J29.1, J30.1, J31.1; also elsewhere on the board
TIM4_CH4_PWM: J27.2; also elsewhere on the board
TIM5_CH1_PWM: J28.3; also elsewhere on the board
TIM5_CH2_PWM: J29.3; also elsewhere on the board
TIM5_CH3_PWM: J30.3; also elsewhere on the board
TIM5_CH4_PWM: J31.3; also elsewhere on the board

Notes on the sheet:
LED
Moteurs

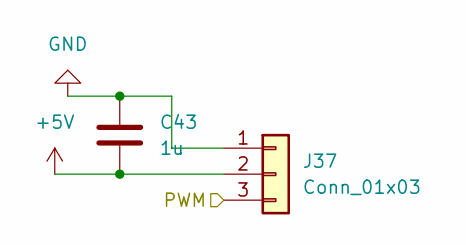
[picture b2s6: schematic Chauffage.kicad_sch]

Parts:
C43: 1u; C_0603_1608Metric
J37: Conn_01x03; JST_EH_B3B-EH-A_1x03_P2.50mm_Vertical

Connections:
+5V: C43.1, J37.2; also elsewhere on the board
GND: C43.2, J37.1; also elsewhere on the board
TIM4_CH2_PWM: J37.3; also elsewhere on the board

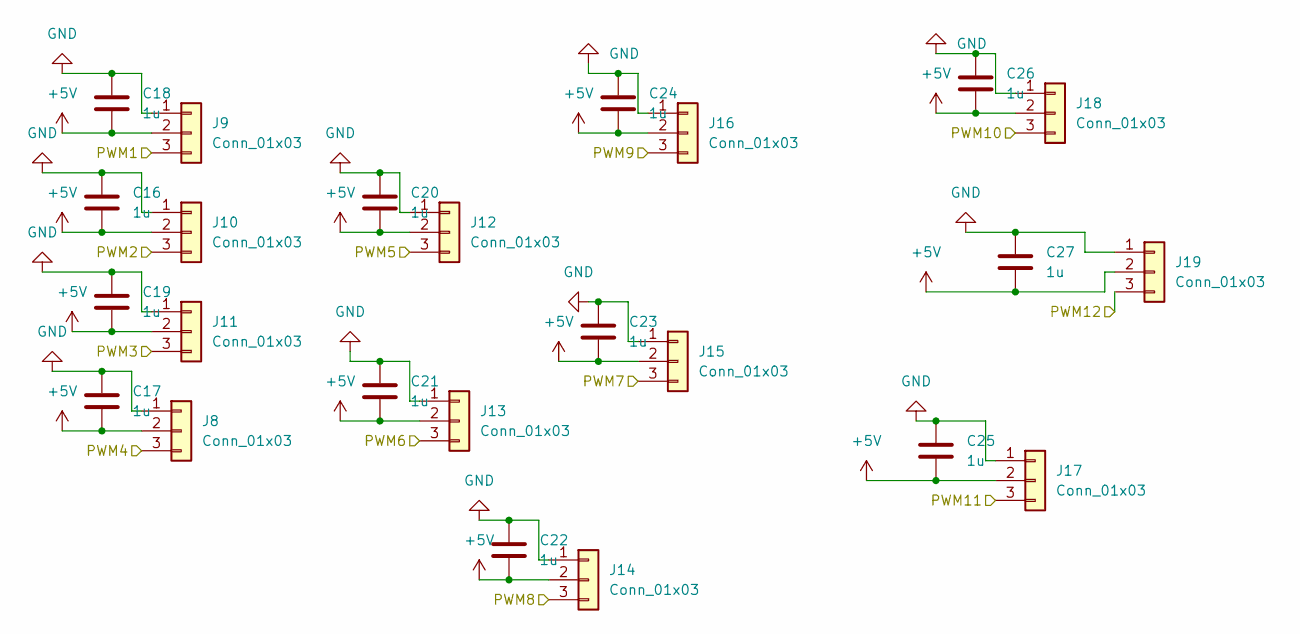
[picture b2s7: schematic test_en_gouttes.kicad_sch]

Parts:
C16, C17, C18, C19, C20, C21, C22, C23, C24, C25, C26, C27: 1u; C_0603_1608Metric
J8, J9, J10, J11, J12, J13, J14, J15, J16, J17, J18, J19: Conn_01x03; JST_EH_B3B-EH-A_1x03_P2.50mm_Vertical

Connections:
+5V: C16.1, C17.1, C18.1, C19.1, C20.1, C21.1, C22.1, C23.1, C24.1, C25.2, C26.2, C27.1, J8.2, J9.2, J10.2, J11.2, J12.2, J13.2, J14.2, J15.2, J16.2, J17.2, J18.2, J19.2; also elsewhere on the board
GND: C16.2, C17.2, C18.2, C19.2, C20.2, C21.2, C22.2, C23.2, C24.2, C25.1, C26.1, C27.2, J8.1, J9.1, J10.1, J11.1, J12.1, J13.1, J14.1, J15.1, J16.1, J17.1, J18.1, J19.1; also elsewhere on the board
TIM1_CH1_PWM: J9.3; also elsewhere on the board
TIM1_CH2_PWM: J10.3; also elsewhere on the board
TIM1_CH3_PWM: J11.3; also elsewhere on the board
TIM1_CH4_PWM: J8.3; also elsewhere on the board
TIM2_CH1_PWM: J12.3; also elsewhere on the board
TIM2_CH2_PWM: J13.3; also elsewhere on the board
TIM2_CH3_PWM: J15.3; also elsewhere on the board
TIM2_CH4_PWM: J14.3; also elsewhere on the board
TIM3_CH1_PWM: J16.3; also elsewhere on the board
TIM3_CH2_PWM: J18.3; also elsewhere on the board
TIM3_CH3_PWM: J17.3; also elsewhere on the board
TIM3_CH4_PWM: J19.3; also elsewhere on the board

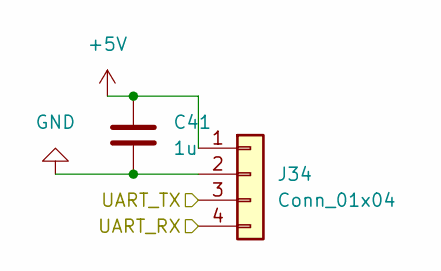
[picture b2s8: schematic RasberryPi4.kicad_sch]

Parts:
C41: 1u; C_0603_1608Metric
J34: Conn_01x04; JST_EH_B4B-EH-A_1x04_P2.50mm_Vertical

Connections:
+5V: C41.2, J34.1; also elsewhere on the board
GND: C41.1, J34.2; also elsewhere on the board
USART3_RX: J34.3; also elsewhere on the board
USART3_TX: J34.4; also elsewhere on the board

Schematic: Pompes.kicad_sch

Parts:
C28, C29: 1u; C_0603_1608Metric
J20, J21, J22, J23: Conn_01x02; JST_EH_B2B-EH-A_1x02_P2.50mm_Vertical
Q1, Q2: NMOS; SOT-23; MPN SQ2310ES
R1, R3: 1k; R_0402_1005Metric
R2, R4: 10k; R_0402_1005Metric

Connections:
+12V: C28.2, C29.1, J20.1, J21.1, J22.1, J23.1; also elsewhere on the board
GND: C28.1, C29.2, J22.2, J23.2, Q1.3 (S), Q2.3 (S), R2.2, R4.2; also elsewhere on the board
GPIO_PUMP_1: R1.2; also elsewhere on the board
GPIO_PUMP_2: R3.2; also elsewhere on the board
unnamed: J20.2, Q1.1 (D)
unnamed: J21.2, Q2.1 (D)
unnamed: Q1.2 (G), R1.1, R2.1
unnamed: Q2.2 (G), R3.1, R4.1

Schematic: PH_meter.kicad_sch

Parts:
C11: 1u; C_0603_1608Metric
J1: Conn_01x03; JST_EH_B3B-EH-A_1x03_P2.50mm_Vertical

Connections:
+5V: C11.1, J1.2; also elsewhere on the board
ADC1_IN10_PH: J1.3; also elsewhere on the board
GND: C11.2, J1.1; also elsewhere on the board

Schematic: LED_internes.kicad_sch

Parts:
C42: 1u; C_0603_1608Metric
J36: Conn_01x03; JST_EH_B3B-EH-A_1x03_P2.50mm_Vertical

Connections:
+5V: C42.2, J36.1; also elsewhere on the board
GND: C42.1, J36.3; also elsewhere on the board
TIM4_CH1_PWM: J36.2; also elsewhere on the board

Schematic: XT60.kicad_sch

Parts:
J33: Conn_01x02; AMASS_XT60-M_1x02_P7.20mm_Vertical
SW2: SW_SPDT; 472123010111; MPN 472123010111

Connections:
+12V: SW2.1 (A); also elsewhere on the board
GND: J33.1; also elsewhere on the board
unnamed: J33.2, SW2.2 (B)

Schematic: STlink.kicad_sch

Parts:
J35: Conn_ST_STDC14; PinHeader_2x07_P1.27mm_Vertical_SMD; MPN STLINK-V3MINIE

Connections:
+3.3V: J35.3 (VCC); also elsewhere on the board
GND: J35.5 (GND), J35.7 (GND), J35.11 (GNDDetect); also elsewhere on the board
NRST: J35.12 (~RST); also elsewhere on the board
SWCLK: J35.6 (JCLK/SWCLK); also elsewhere on the board
SWDIO: J35.4 (JTMS/SWDIO); also elsewhere on the board
UART_DEBUG_RX: J35.13 (VCP_RX); also elsewhere on the board
UART_DEBUG_TX: J35.14 (VCP_TX); also elsewhere on the board

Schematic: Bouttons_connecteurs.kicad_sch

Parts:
J2: Conn_01x06; JST_EH_B6B-EH-A_1x06_P2.50mm_Vertical

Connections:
GPIO_BTN_1: J2.1; also elsewhere on the board
GPIO_BTN_2: J2.2; also elsewhere on the board
GPIO_BTN_3: J2.3; also elsewhere on the board
GPIO_BTN_4: J2.4; also elsewhere on the board
GPIO_BTN_5: J2.5; also elsewhere on the board
GPIO_BTN_6: J2.6; also elsewhere on the board

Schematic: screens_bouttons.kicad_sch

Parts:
C15: 1u; C_0603_1608Metric
J6, J7: Conn_01x06; JST_EH_B6B-EH-A_1x06_P2.50mm_Vertical

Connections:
+3.3V: C15.2, J6.5; also elsewhere on the board
GND: C15.1, J6.6; also elsewhere on the board
GPIO_D/C: J6.1; also elsewhere on the board
GPIO_RES: J6.2; also elsewhere on the board
GPIO_SPI_CS_1: J7.1; also elsewhere on the board
GPIO_SPI_CS_2: J7.2; also elsewhere on the board
GPIO_SPI_CS_3: J7.3; also elsewhere on the board
GPIO_SPI_CS_4: J7.4; also elsewhere on the board
GPIO_SPI_CS_5: J7.5; also elsewhere on the board
GPIO_SPI_CS_6: J7.6; also elsewhere on the board
SPI2_MOSI: J6.3; also elsewhere on the board
SPI2_SCK: J6.4; also elsewhere on the board

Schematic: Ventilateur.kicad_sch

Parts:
C12: 1u; C_0603_1608Metric
J3: Conn_01x02; JST_EH_B2B-EH-A_1x02_P2.50mm_Vertical

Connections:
+12V: C12.2, J3.1; also elsewhere on the board
GND: C12.1, J3.2; also elsewhere on the board

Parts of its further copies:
C13, C14, C40: 1u; C_0603_1608Metric
J4, J5, J32: Conn_01x02; JST_EH_B2B-EH-A_1x02_P2.50mm_Vertical

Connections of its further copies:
+12V: C13.2, C14.2, C40.2, J4.1, J5.1, J32.1; also elsewhere on the board
GND: C13.1, C14.1, C40.1, J4.2, J5.2, J32.2; also elsewhere on the board
